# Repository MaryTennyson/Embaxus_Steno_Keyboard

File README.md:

# Embaxus Steno Keyboard

A 28-key stenography keyboard PCB with per-key RGB, designed in KiCad 10.

- **MCU:** Waveshare RP2040-Zero (mounted on the back, USB-C at the right edge)
- **Switches:** 28× Cherry MX-compatible, PCB mount
- **Lighting:** 32× SK6812MINI-E reverse-mount RGB LEDs (28 under the keys + 4 standalone)
- **Board:** 2 layers, 273.84 × 85.73 mm, 1.6 mm FR-4

| Top | Bottom |
|---|---|
|  |  |

The full schematic is in [`docs/schematic.pdf`](docs/schematic.pdf).

## Repository layout

| Path | Contents |
|---|---|
| `hardware/` | KiCad 10 project: schematic, PCB, design rules (`.kicad_dru`) |
| `production/embaxus-steno-keyboard-gerbers.zip` | Ready-to-order Gerber + Excellon drill files |
| `production/gerber/` | The same fabrication files, unzipped |
| `docs/` | Schematic PDF and board renders |

## Electrical overview

### Key matrix (11 columns × 3 rows, COL2ROW)

Each switch has a 1N4148 diode: anode on the switch, cathode on the row.

| RP2040-Zero pin | Net |
|---|---|
| GP0 – GP10 | COLUMN0 – COLUMN10 |
| GP11 | ROW0 |
| GP12 | ROW1 |
| GP13 | ROW2 (thumb row) |
| GP14 | LED data (through R1) |

### RGB LEDs

- Data path: **GP14 → R1 (330 Ω) → LED_1 → LED_2 → … → LED_32**. The LED numbers follow the chain order.
- **LED_1 supply diode (D29, 1N4148):** LED_1 is powered from 5 V through D29, so it runs at about 4.3 V. Its input threshold (0.7 × VDD) drops to about 3.0 V, so the RP2040's 3.3 V data is read reliably. LED_1 re-drives the data at full level for the rest of the chain.
- **Decoupling:** one 100 nF capacitor per LED, placed next to its LED.
- **Current:** at full white the 32 LEDs draw roughly 1.15 A (12 mA per colour channel), more than USB normally supplies. **Limit brightness in firmware.**

### Expansion header J1 (unpopulated, 2.54 mm)

| J1 pin | Signal |
|---|---|
| 1 | +5V |
| 2 | GND |
| 3 | 3V3 |
| 4 | GP29 |
| 5 | GP28 |
| 6 | GP27 |
| 7 | GP26 |
| 8 | GP15 |

Pins 1 and 2 are next to each other; take care not to bridge 5 V to GND when soldering wires.

## Bill of materials

| Qty | Ref | Part | Footprint |
|---|---|---|---|
| 28 | S1–S28 | MX-compatible switch | MX PCB 1.00u |
| 29 | D1–D29 | 1N4148 | DO-35, 7.62 mm pitch |
| 32 | LED_1–LED_32 | SK6812MINI-E | Reverse mount, 3.2 × 2.8 mm |
| 32 | C1–C32 | 100 nF ceramic | Disc, 2.5 mm pitch |
| 1 | U2 | RP2040-Zero | Through-hole module |
| 1 | R1 | 330 Ω, 1/4 W | Axial, 7.62 mm pitch |
| 1 | J1 | 1×8 pin header (optional) | 2.54 mm |
| 4 | H1–H4 | M2 mounting holes | 2.2 mm NPTH |

## Fabrication

Upload `production/embaxus-steno-keyboard-gerbers.zip` to your PCB fab. Settings used:

- 2 layers, 1.6 mm, 1 oz copper, HASL (lead free)
- Min track / spacing: 0.2 mm (use the fab's 6/6 mil option)
- Min hole: 0.3 mm (vias 0.3 mm drill / 0.6 mm pad)
- The board has **32 internal rectangular cutouts** for the reverse-mount LEDs on the Edge.Cuts layer. Some LED pads are about 0.25 mm from these cutouts; this comes from KiCad's standard SK6812MINI-E footprint and is allowed for LED pads only by a custom rule in `hardware/embaxus-steno-keyboard.kicad_dru`.

## Assembly notes

- **SK6812MINI-E LEDs are moisture sensitive (MSL 5a).** Solder them within about 24 h of opening the bag, or bake at 70 °C for 12 h first.
- The LEDs are **reverse mount**: the body goes up through the cutout, and the four legs are soldered to the pads on the back. Do not cut the legs.
- Handle the LEDs by their sides; the silicone lens is soft.
- If R1 is not fitted, bridge its two holes with a wire. Otherwise no data reaches the LEDs.

## Firmware notes (QMK / Vial)

- Diode direction: `COL2ROW`.
- Matrix: columns GP0–GP10, rows GP11–GP13.
- RGB: WS2812 driver on GP14, 32 LEDs, chain order LED_1 → LED_32 as on the silkscreen. LED_29–LED_32 are not under keys.
- Set a brightness cap (for example `RGB_MATRIX_MAXIMUM_BRIGHTNESS` around 100–120) to stay within USB current.

## Editing the design

The project opens in **KiCad 10**. Symbols and footprints are embedded in the schematic and PCB files. To edit library parts, install the [ScottoKeebs KiCad libraries](https://github.com/joe-scotto/scottokeebs) used for the switch, MCU and diode placeholders.

## License

No license has been chosen yet.

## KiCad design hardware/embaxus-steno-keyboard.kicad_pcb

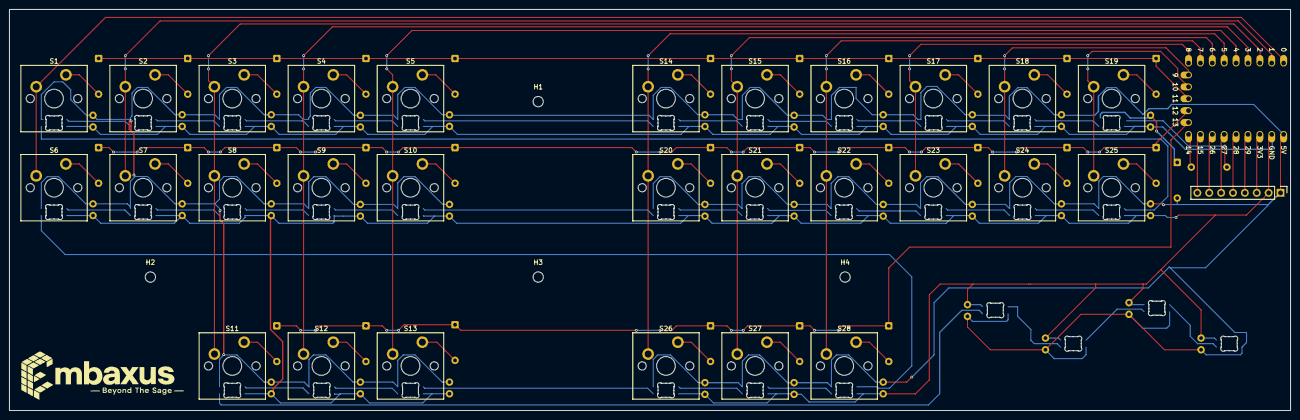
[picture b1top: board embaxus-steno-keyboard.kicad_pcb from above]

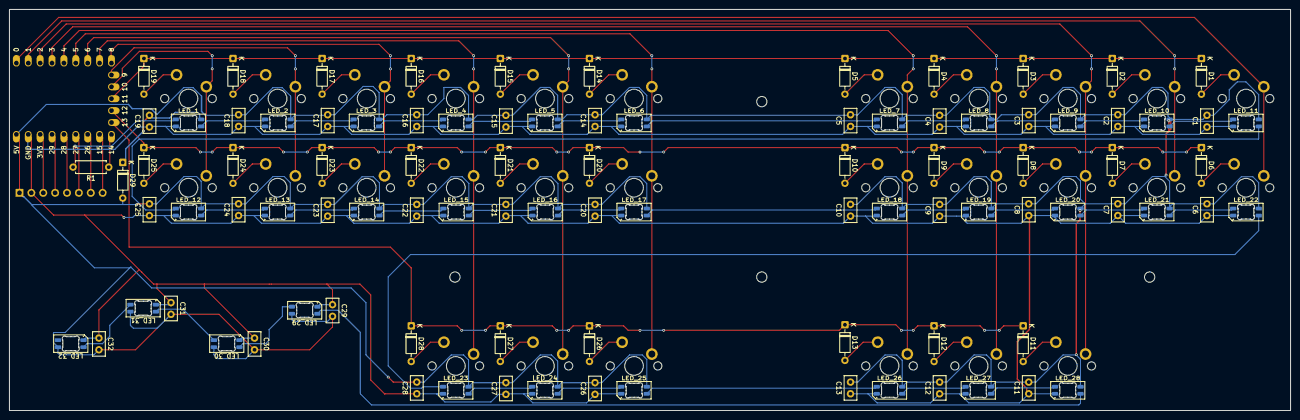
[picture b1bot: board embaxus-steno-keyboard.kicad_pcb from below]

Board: 2 copper layers, 273.8 x 85.7 mm, 128 parts (95 on the bottom side), 84 nets.

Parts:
C1, C2, C3, C4, C5, C6, C7, C8, C9, C10, C11, C12, C13, C14, C15, C16, C17, C18, C19, C20, C21, C22, C23, C24, C25, C26, C27, C28, C29, C30, C31, C32: 100nF; C_Disc_D5.0mm_W2.5mm_P2.50mm
D1, D2, D3, D4, D5, D6, D7, D8, D9, D10, D11, D12, D13, D14, D15, D16, D17, D18, D19, D20, D21, D22, D23, D24, D25, D26, D27, D28, D29: 1N4148; D_DO-35_SOD27_P7.62mm_Horizontal
H1, H2: M2; MountingHole_2.2mm_M2
H3: M3; MountingHole_2.2mm_M2
H4: M4; MountingHole_2.2mm_M2
J1: Conn_01x08_Pin; PinHeader_1x08_P2.54mm_Vertical
LED_1, LED_2, LED_3, LED_4, LED_5, LED_6, LED_7, LED_8, LED_9, LED_10, LED_11, LED_12, LED_13, LED_14, LED_15, LED_16, LED_17, LED_18, LED_19, LED_20, LED_21, LED_22, LED_23, LED_24, LED_25, LED_26, LED_27, LED_28, LED_29, LED_30, LED_31, LED_32: SK6812MINI-E; LED_SK6812MINI-E_3.2x2.8mm_P1.5mm_ReverseMount
R1: 330; R_Axial_DIN0207_L6.3mm_D2.5mm_P7.62mm_Horizontal
S1, S2, S3, S4, S5, S6, S7, S8, S9, S10, S11, S12, S13, S14, S15, S16, S17, S18, S19, S20, S21, S22, S23, S24, S25, S26, S27, S28: MX_PCB_1.00u
U2: RP2040_Zero

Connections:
+5V: C1.2 (A), C2.2 (A), C3.2 (A), C4.2 (A), C5.2 (A), C6.2 (A), C7.2 (A), C8.2 (A), C9.2 (A), C10.2 (A), C11.2 (A), C12.2 (A), C13.2 (A), C14.2 (A), C15.2 (A), C16.2 (A), C17.2 (A), C18.2 (A), C20.2 (A), C21.2 (A), C22.2 (A), C23.2 (A), C24.2 (A), C25.2 (A), C26.2 (A), C27.2 (A), C28.2 (A), C29.2 (A), C30.2 (A), C31.2 (A), C32.2 (A), D29.2 (A), J1.1, LED_2.3 (VDD), LED_3.3 (VDD), LED_4.3 (VDD), LED_5.3 (VDD), LED_6.3 (VDD), LED_7.3 (VDD), LED_8.3 (VDD), LED_9.3 (VDD), LED_10.3 (VDD), LED_11.3 (VDD), LED_12.3 (VDD), LED_13.3 (VDD), LED_14.3 (VDD), LED_15.3 (VDD), LED_16.3 (VDD), LED_17.3 (VDD), LED_18.3 (VDD), LED_19.3 (VDD), LED_20.3 (VDD), LED_21.3 (VDD), LED_22.3 (VDD), LED_23.3 (VDD), LED_24.3 (VDD), LED_25.3 (VDD), LED_26.3 (VDD), LED_27.3 (VDD), LED_28.3 (VDD), LED_29.3 (VDD), LED_30.3 (VDD), LED_31.3 (VDD), LED_32.3 (VDD), U2.23 (5V)
COLUMN0: S1.1, S6.1, U2.1 (0)
COLUMN1: S2.1, S7.1, U2.2 (1)
COLUMN2: S3.1, S8.1, S11.1, U2.3 (2)
COLUMN3: S4.1, S9.1, S12.1, U2.4 (3)
COLUMN4: S5.1, S10.1, S13.1, U2.5 (4)
COLUMN5: S14.1, S20.1, S26.1, U2.6 (5)
COLUMN6: S15.1, S21.1, S27.1, U2.7 (6)
COLUMN7: S16.1, S22.1, S28.1, U2.8 (7)
COLUMN8: S17.1, S23.1, U2.9 (8)
COLUMN9: S18.1, S24.1, U2.10 (9)
COLUMN10: S19.1, S25.1, U2.11 (10)
GND: C1.1 (K), C2.1 (K), C3.1 (K), C4.1 (K), C5.1 (K), C6.1 (K), C7.1 (K), C8.1 (K), C9.1 (K), C10.1 (K), C11.1 (K), C12.1 (K), C13.1 (K), C14.1 (K), C15.1 (K), C16.1 (K), C17.1 (K), C18.1 (K), C19.1 (K), C20.1 (K), C21.1 (K), C22.1 (K), C23.1 (K), C24.1 (K), C25.1 (K), C26.1 (K), C27.1 (K), C28.1 (K), C29.1 (K), C30.1 (K), C31.1 (K), C32.1 (K), J1.2, LED_1.1 (VSS), LED_2.1 (VSS), LED_3.1 (VSS), LED_4.1 (VSS), LED_5.1 (VSS), LED_6.1 (VSS), LED_7.1 (VSS), LED_8.1 (VSS), LED_9.1 (VSS), LED_10.1 (VSS), LED_11.1 (VSS), LED_12.1 (VSS), LED_13.1 (VSS), LED_14.1 (VSS), LED_15.1 (VSS), LED_16.1 (VSS), LED_17.1 (VSS), LED_18.1 (VSS), LED_19.1 (VSS), LED_20.1 (VSS), LED_21.1 (VSS), LED_22.1 (VSS), LED_23.1 (VSS), LED_24.1 (VSS), LED_25.1 (VSS), LED_26.1 (VSS), LED_27.1 (VSS), LED_28.1 (VSS), LED_29.1 (VSS), LED_30.1 (VSS), LED_31.1 (VSS), LED_32.1 (VSS), U2.22 (GND)
LED1_VDD: C19.2 (A), D29.1 (K), LED_1.3 (VDD)
LED11_DOUT: LED_11.4 (DOUT), LED_12.2 (DIN)
LED22_DOUT: LED_22.4 (DOUT), LED_23.2 (DIN)
LED_DATA: LED_1.2 (DIN), R1.2
unnamed: D1.2 (A), S1.2
unnamed: D2.2 (A), S2.2
unnamed: D3.2 (A), S3.2
unnamed: D4.2 (A), S4.2
unnamed: D5.2 (A), S5.2
unnamed: D6.2 (A), S6.2
unnamed: D7.2 (A), S7.2
unnamed: D8.2 (A), S8.2
unnamed: D9.2 (A), S9.2
unnamed: D10.2 (A), S10.2
unnamed: D11.2 (A), S11.2
unnamed: D12.2 (A), S12.2
unnamed: D13.2 (A), S13.2
unnamed: D14.2 (A), S14.2
unnamed: D15.2 (A), S15.2
unnamed: D16.2 (A), S16.2
unnamed: D17.2 (A), S17.2
unnamed: D18.2 (A), S18.2
unnamed: D19.2 (A), S19.2
unnamed: D20.2 (A), S20.2
unnamed: D21.2 (A), S21.2
unnamed: D22.2 (A), S22.2
unnamed: D23.2 (A), S23.2
unnamed: D24.2 (A), S24.2
unnamed: D25.2 (A), S25.2
unnamed: D26.2 (A), S26.2
unnamed: D27.2 (A), S27.2
unnamed: D28.2 (A), S28.2
unnamed: J1.3, U2.21 (3V3)
unnamed: J1.4, U2.20 (29)
unnamed: J1.5, U2.19 (28)
unnamed: J1.6, U2.18 (27)
unnamed: J1.7, U2.17 (26)
unnamed: J1.8, U2.16 (15)
unnamed: LED_1.4 (DOUT), LED_2.2 (DIN)
unnamed: LED_2.4 (DOUT), LED_3.2 (DIN)
unnamed: LED_3.4 (DOUT), LED_4.2 (DIN)
unnamed: LED_4.4 (DOUT), LED_5.2 (DIN)
unnamed: LED_5.4 (DOUT), LED_6.2 (DIN)
unnamed: LED_6.4 (DOUT), LED_7.2 (DIN)
unnamed: LED_7.4 (DOUT), LED_8.2 (DIN)
unnamed: LED_8.4 (DOUT), LED_9.2 (DIN)
unnamed: LED_9.4 (DOUT), LED_10.2 (DIN)
unnamed: LED_10.4 (DOUT), LED_11.2 (DIN)
unnamed: LED_12.4 (DOUT), LED_13.2 (DIN)
unnamed: LED_13.4 (DOUT), LED_14.2 (DIN)
unnamed: LED_14.4 (DOUT), LED_15.2 (DIN)
unnamed: LED_15.4 (DOUT), LED_16.2 (DIN)
unnamed: LED_16.4 (DOUT), LED_17.2 (DIN)
unnamed: LED_17.4 (DOUT), LED_18.2 (DIN)
unnamed: LED_18.4 (DOUT), LED_19.2 (DIN)
unnamed: LED_19.4 (DOUT), LED_20.2 (DIN)
unnamed: LED_20.4 (DOUT), LED_21.2 (DIN)
unnamed: LED_21.4 (DOUT), LED_22.2 (DIN)
unnamed: LED_23.4 (DOUT), LED_24.2 (DIN)
unnamed: LED_24.4 (DOUT), LED_25.2 (DIN)
unnamed: LED_25.4 (DOUT), LED_26.2 (DIN)
unnamed: LED_26.4 (DOUT), LED_27.2 (DIN)
unnamed: LED_27.4 (DOUT), LED_28.2 (DIN)
unnamed: LED_28.4 (DOUT), LED_29.2 (DIN)
unnamed: LED_29.4 (DOUT), LED_30.2 (DIN)
unnamed: LED_30.4 (DOUT), LED_31.2 (DIN)
unnamed: LED_31.4 (DOUT), LED_32.2 (DIN)
unnamed: R1.1, U2.15 (14)
ROW0: D1.1 (K), D2.1 (K), D3.1 (K), D4.1 (K), D5.1 (K), D14.1 (K), D15.1 (K), D16.1 (K), D17.1 (K), D18.1 (K), D19.1 (K), U2.12 (11)
ROW1: D6.1 (K), D7.1 (K), D8.1 (K), D9.1 (K), D10.1 (K), D20.1 (K), D21.1 (K), D22.1 (K), D23.1 (K), D24.1 (K), D25.1 (K), U2.13 (12)
ROW2: D11.1 (K), D12.1 (K), D13.1 (K), D26.1 (K), D27.1 (K), D28.1 (K), U2.14 (13)
